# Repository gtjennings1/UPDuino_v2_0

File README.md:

# UPDuino_v2_0
UPDuino v2.0 - PCB Design Files, Designs, Documentation

UPDuino v2.0 is a small, low cost FPGA board.  
It is the same board as UPDuino v1.0, but v2.0 has a built-in USB programmer
(Similar to Arduino Pro Mini vs Arduino Nano microcontroller boards respectively).

Gnarly Grey UPDuino v2.0 Board Features

    Lattice UltraPlus FPGA
        5.3K LUTs, 1Mb SPRAM, 120Kb DPRAM, 8 Multipliers
        
    FTDI FT232H USB to SPI Device
    
    34 GPIO on 0.1” headers
    
    SPI Flash, RGB LED, 3.3V and 1.2V Regulators
    
    Open source schematic and layout using free Eagle PCB design tools
        Download Schematic & Layout
        Schematic PDF
        Programming Instructions
        RGB LED Example Project

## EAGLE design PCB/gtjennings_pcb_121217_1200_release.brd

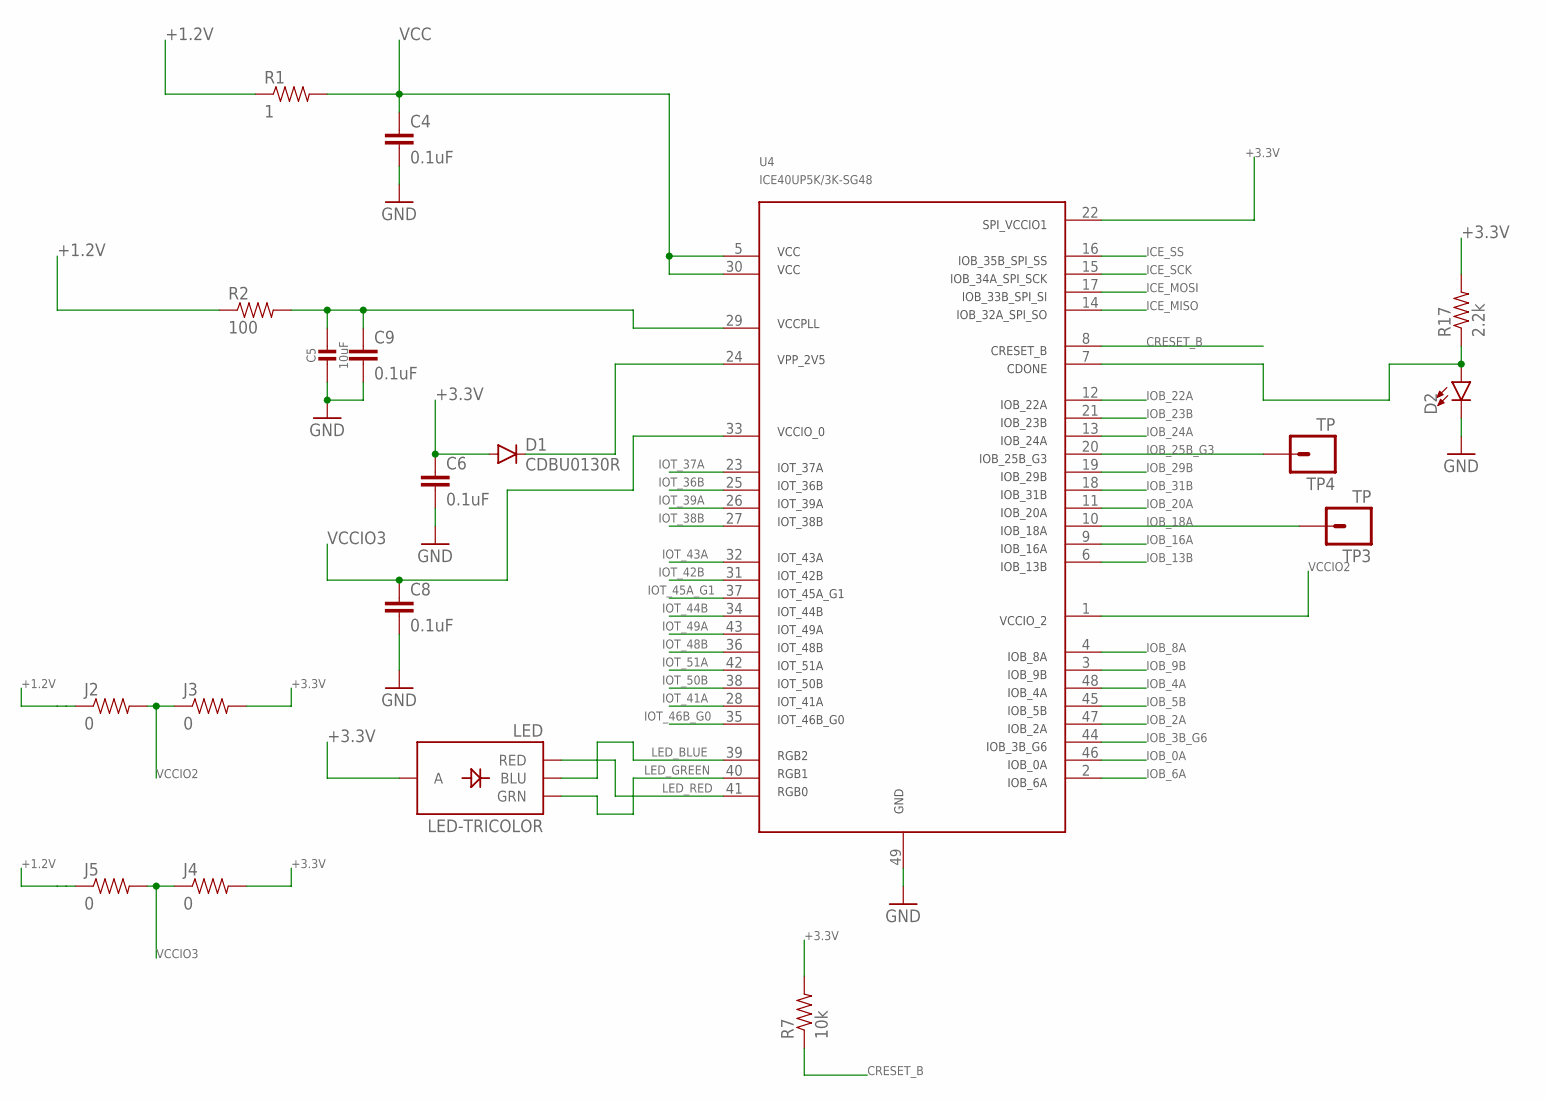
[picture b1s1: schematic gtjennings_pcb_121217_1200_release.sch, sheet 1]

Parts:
C4, C6, C8, C9: 0.1uF; 0603-CAP
C5: 10uF; 0603-NO
D1: CDBU0130R; SOD523
D2: LED0603; LED-0603
J2, J3, J4, J5: 0; 0603-RES
LED: LED-TRICOLOR; LED-TRICOLOR-SMD
R1: 1; 0603-RES
R2: 100; 0603-RES
R7: 10k; 0603-RES
R17: 2.2k; 0603-RES
TP3, TP4: TP
U4: ICE40UP5K/3K-SG48

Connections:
+1.2V: J2.1, J5.1, R1.1, R2.1; also elsewhere on the board
+3.3V: C6.1, D1.A, J3.2, J4.2, LED.A, R7.2, R17.2, U4.22; also elsewhere on the board
CRESET_B: R7.1, U4.8; also elsewhere on the board
GND: C4.2, C5.2, C6.2, C8.2, C9.2, D2.C, U4.49; also elsewhere on the board
ICE_MISO: U4.14; also elsewhere on the board
ICE_MOSI: U4.17; also elsewhere on the board
ICE_SCK: U4.15; also elsewhere on the board
ICE_SS: U4.16; also elsewhere on the board
IOB_0A: U4.46; also elsewhere on the board
IOB_2A: U4.47; also elsewhere on the board
IOB_3B_G6: U4.44; also elsewhere on the board
IOB_4A: U4.48; also elsewhere on the board
IOB_5B: U4.45; also elsewhere on the board
IOB_6A: U4.2; also elsewhere on the board
IOB_8A: U4.4; also elsewhere on the board
IOB_9B: U4.3; also elsewhere on the board
IOB_13B: U4.6; also elsewhere on the board
IOB_16A: U4.9; also elsewhere on the board
IOB_18A: TP3.1, U4.10
IOB_20A: U4.11; also elsewhere on the board
IOB_22A: U4.12; also elsewhere on the board
IOB_23B: U4.21; also elsewhere on the board
IOB_24A: U4.13; also elsewhere on the board
IOB_25B_G3: TP4.1, U4.20
IOB_29B: U4.19; also elsewhere on the board
IOB_31B: U4.18; also elsewhere on the board
IOT_36B: U4.25; also elsewhere on the board
IOT_37A: U4.23; also elsewhere on the board
IOT_38B: U4.27; also elsewhere on the board
IOT_39A: U4.26; also elsewhere on the board
IOT_41A: U4.28; also elsewhere on the board
IOT_42B: U4.31; also elsewhere on the board
IOT_43A: U4.32; also elsewhere on the board
IOT_44B: U4.34; also elsewhere on the board
IOT_45A_G1: U4.37; also elsewhere on the board
IOT_46B_G0: U4.35; also elsewhere on the board
IOT_48B: U4.36; also elsewhere on the board
IOT_49A: U4.43; also elsewhere on the board
IOT_50B: U4.38; also elsewhere on the board
IOT_51A: U4.42; also elsewhere on the board
LED_BLUE: LED.B (BLU), U4.39
LED_GREEN: LED.G (GRN), U4.40
LED_RED: LED.R (RED), U4.41
unnamed: C5.1, C9.1, R2.2, U4.29
unnamed: D1.C, U4.24
unnamed: D2.A, R17.1, U4.7
VCC: C4.1, R1.2, U4.5, U4.30
VCCIO2: J2.2, J3.1, U4.1
VCCIO3: C8.1, J4.1, J5.2, U4.33

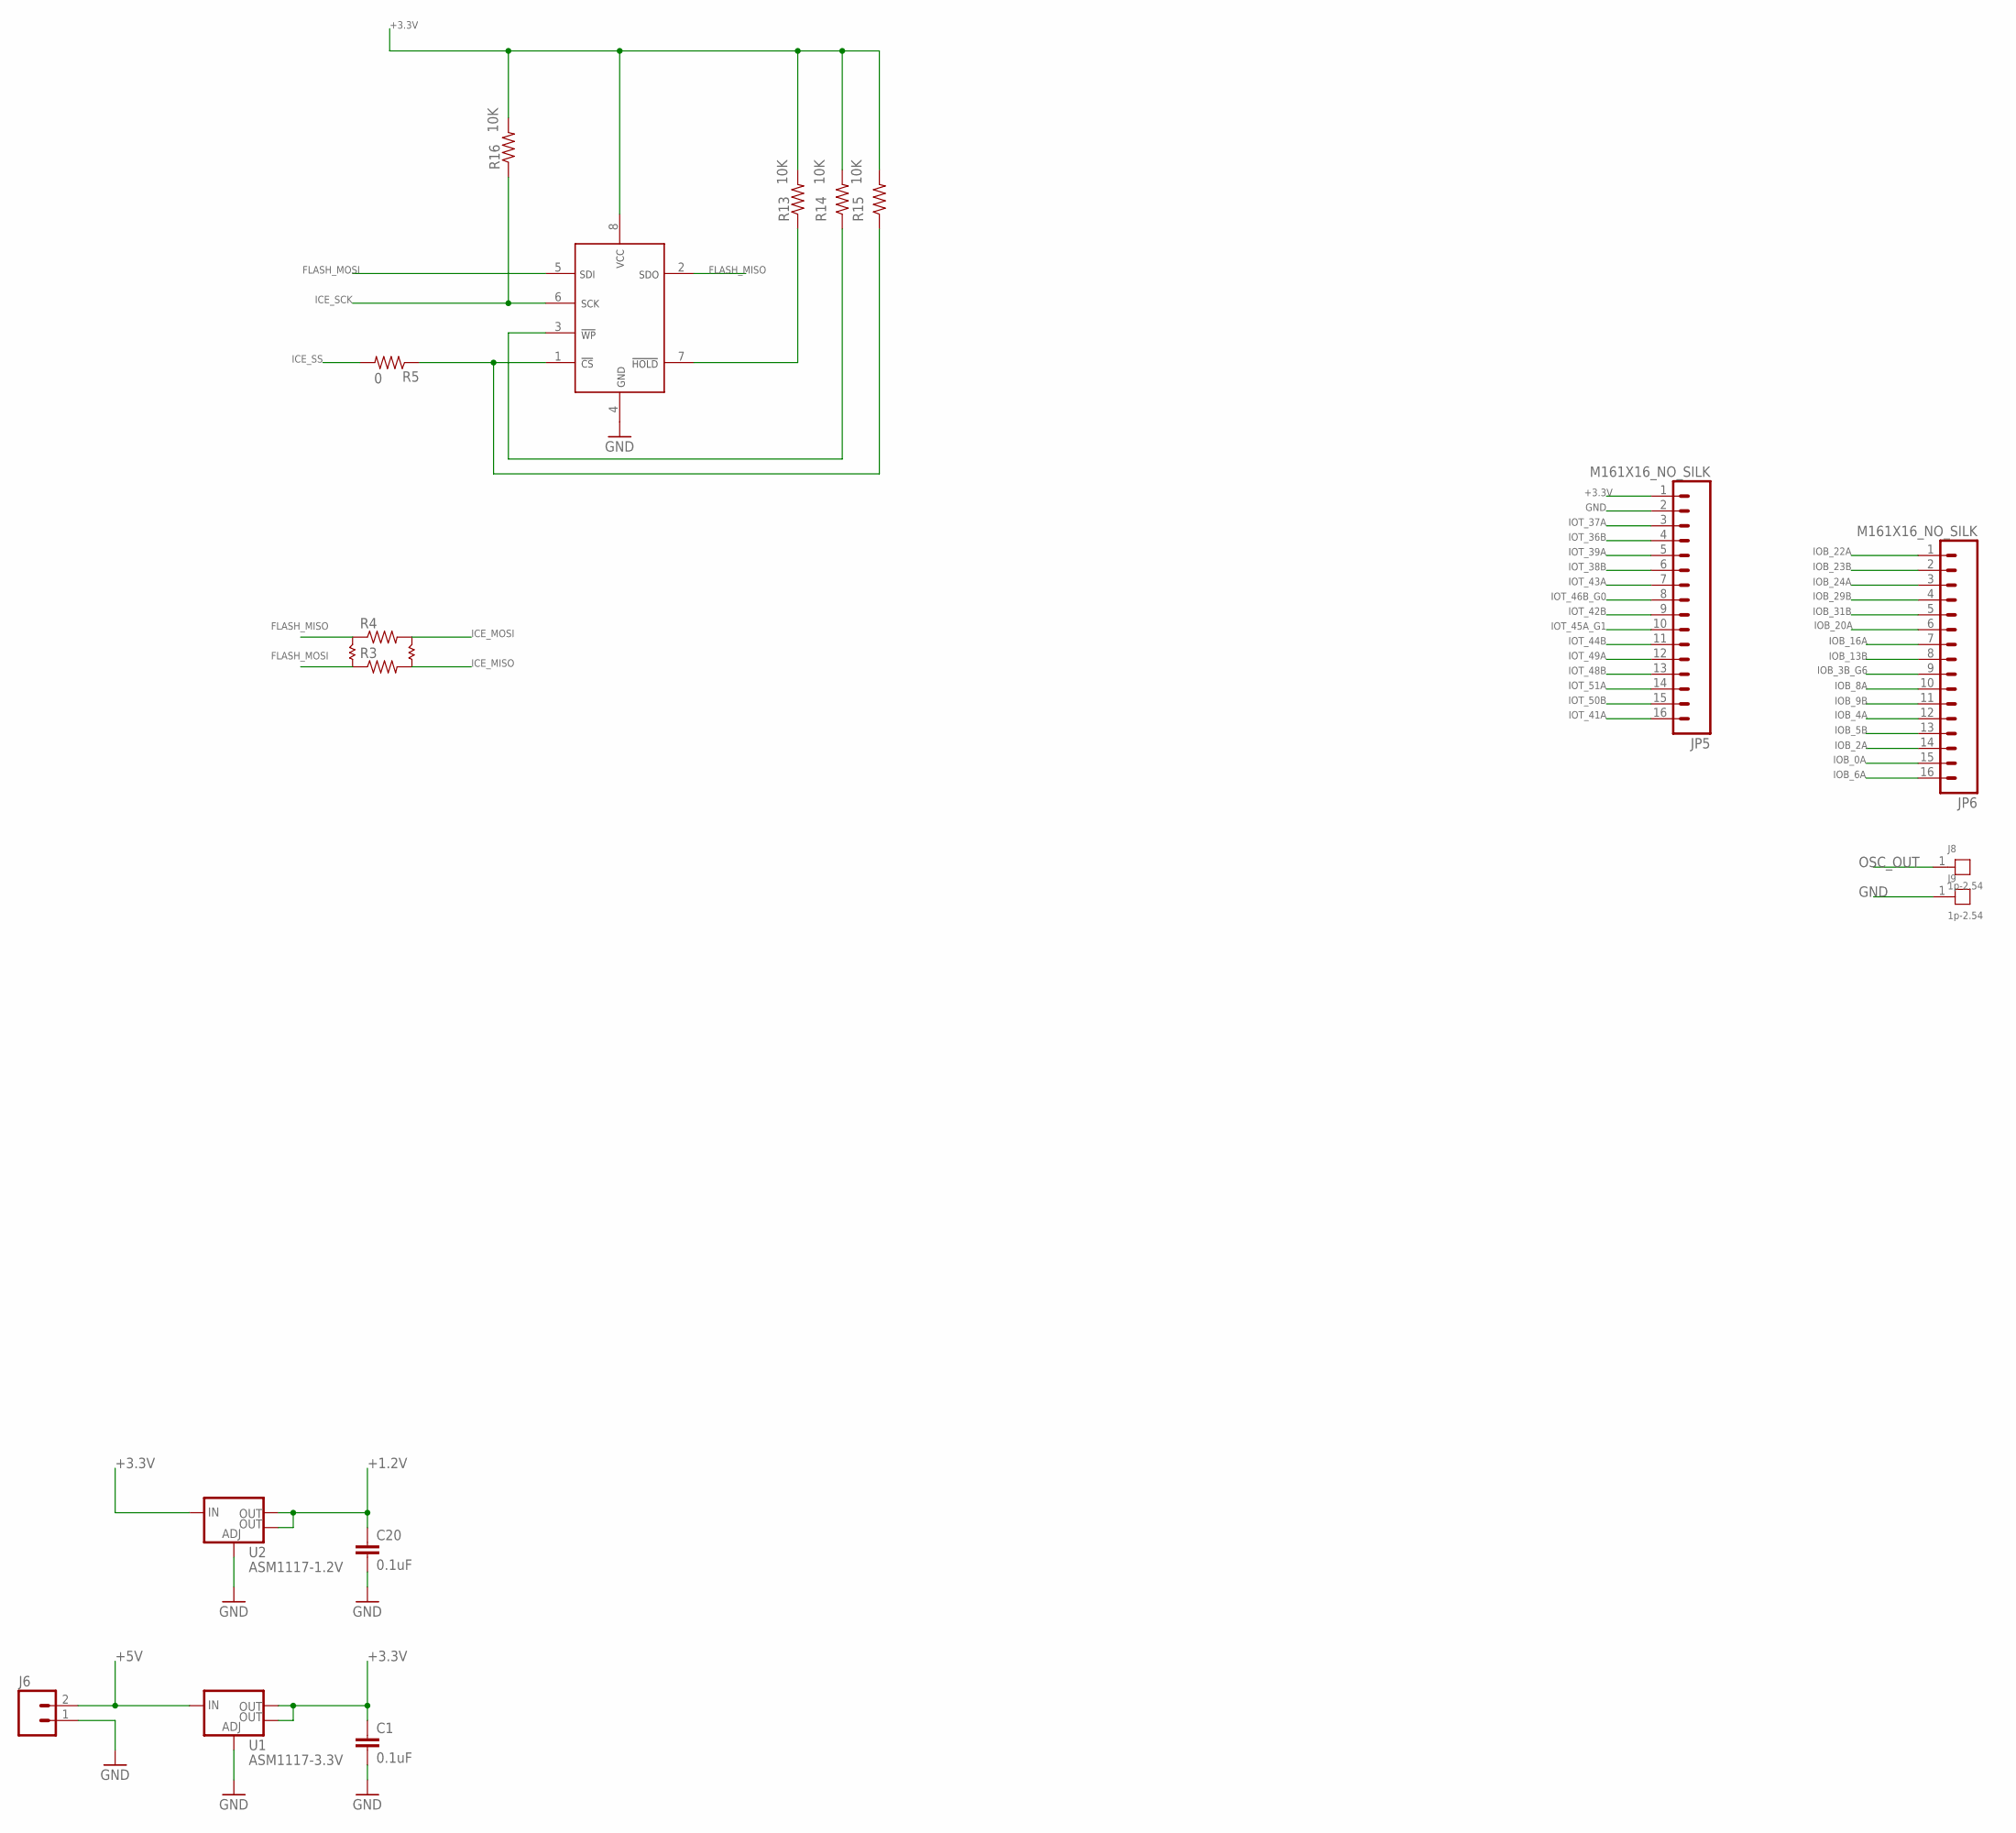
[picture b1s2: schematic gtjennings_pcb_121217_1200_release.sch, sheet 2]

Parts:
C1, C20: 0.1uF; 0603-CAP
J6: M02PTH; 1X02
J8, J9: 1p-2.54; 1P-65/35MIL
JP5, JP6: M161X16_NO_SILK; 1X16_NO_SILK
R3, R4: RESISTOR0805-RES; 0805
R5: 0; 0805
R13, R14, R15, R16: 10K; 0603-RES
U1: ASM1117-3.3V; SOT223
U2: ASM1117-1.2V; SOT223
U3: N25Q032A13ESC40F-ND; SO8

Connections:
+1.2V: C20.1, U2.2 (OUT), U2.4 (OUT); also elsewhere on the board
+3.3V: C1.1, JP5.1, R13.2, R14.2, R15.2, R16.2, U1.2 (OUT), U1.4 (OUT), U2.3 (IN), U3.8; also elsewhere on the board
+5V: J6.2, U1.3 (IN); also elsewhere on the board
FLASH_MISO: R4.1, U3.2; also elsewhere on the board
FLASH_MOSI: R3.1, U3.5; also elsewhere on the board
GND: C1.2, C20.2, J6.1, J9.1, JP5.2, U1.1 (ADJ), U2.1 (ADJ), U3.4; also elsewhere on the board
ICE_MISO: R3.2; also elsewhere on the board
ICE_MOSI: R4.2; also elsewhere on the board
ICE_SCK: R16.1, U3.6; also elsewhere on the board
ICE_SS: R5.2; also elsewhere on the board
IOB_0A: JP6.15; also elsewhere on the board
IOB_2A: JP6.14; also elsewhere on the board
IOB_3B_G6: JP6.9; also elsewhere on the board
IOB_4A: JP6.12; also elsewhere on the board
IOB_5B: JP6.13; also elsewhere on the board
IOB_6A: JP6.16; also elsewhere on the board
IOB_8A: JP6.10; also elsewhere on the board
IOB_9B: JP6.11; also elsewhere on the board
IOB_13B: JP6.8; also elsewhere on the board
IOB_16A: JP6.7; also elsewhere on the board
IOB_20A: JP6.6; also elsewhere on the board
IOB_22A: JP6.1; also elsewhere on the board
IOB_23B: JP6.2; also elsewhere on the board
IOB_24A: JP6.3; also elsewhere on the board
IOB_29B: JP6.4; also elsewhere on the board
IOB_31B: JP6.5; also elsewhere on the board
IOT_36B: JP5.4; also elsewhere on the board
IOT_37A: JP5.3; also elsewhere on the board
IOT_38B: JP5.6; also elsewhere on the board
IOT_39A: JP5.5; also elsewhere on the board
IOT_41A: JP5.16; also elsewhere on the board
IOT_42B: JP5.9; also elsewhere on the board
IOT_43A: JP5.7; also elsewhere on the board
IOT_44B: JP5.11; also elsewhere on the board
IOT_45A_G1: JP5.10; also elsewhere on the board
IOT_46B_G0: JP5.8; also elsewhere on the board
IOT_48B: JP5.13; also elsewhere on the board
IOT_49A: JP5.12; also elsewhere on the board
IOT_50B: JP5.15; also elsewhere on the board
IOT_51A: JP5.14; also elsewhere on the board
unnamed: R13.1, U3.7
unnamed: R14.1, U3.3
unnamed: R5.1, R15.1, U3.1
OSC_OUT: J8.1; also elsewhere on the board

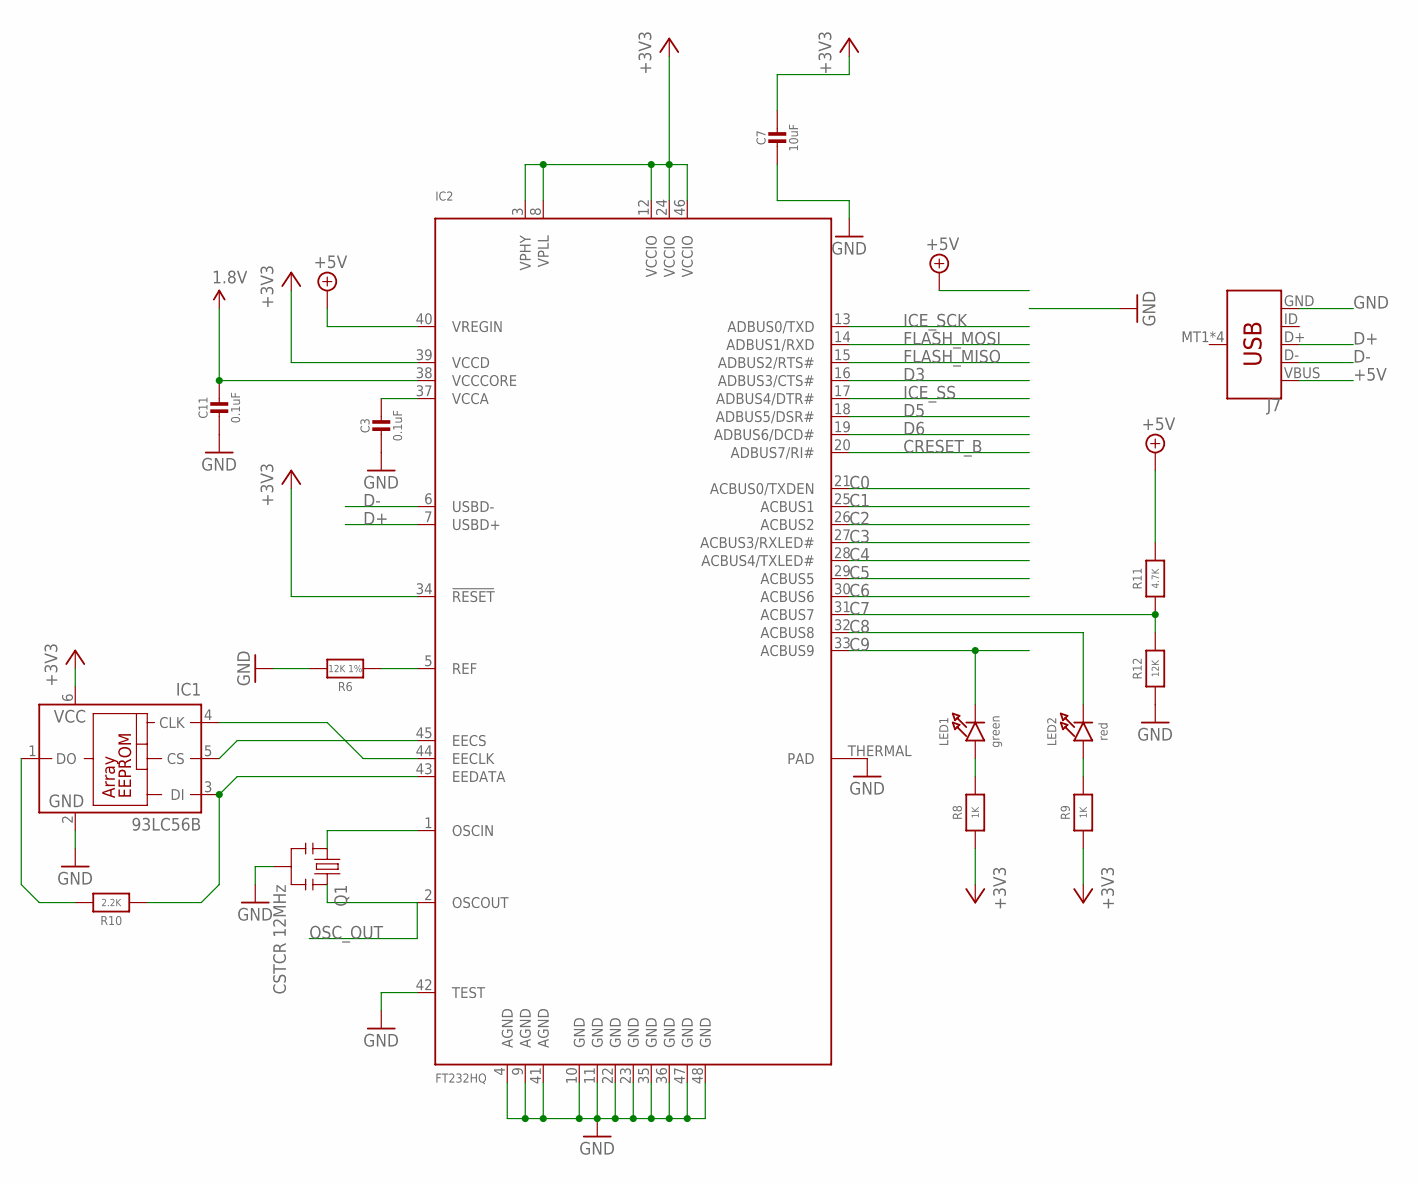
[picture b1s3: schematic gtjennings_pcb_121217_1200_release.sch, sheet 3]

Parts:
C3: 0.1uF; 0603-NO
C7: 10uF; 0603-NO
C11: 0.1uF; 0603-MINI
IC1: 93LC56B; SOT23-6
IC2: FT232HQ; QFN48_8MM
J7: USB_MICRO-B_SMT; USB-MICROB
LED1: green; CHIPLED_0805_NOOUTLINE
LED2: red; CHIPLED_0805_NOOUTLINE
Q1: CSTCR 12MHz; RESONATOR-SMD
R6: 12K 1%; _0603
R8, R9: 1K; 0603-MINI
R10: 2.2K; _0805MP
R11: 4.7K; 0603-MINI
R12: 12K; 0603-MINI

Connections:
1.8V: C11.1, IC2.38 (VCCCORE)
+3V3: C7.1, IC1.6 (VCC), IC2.3 (VPHY), IC2.8 (VPLL), IC2.12 (VCCIO), IC2.24 (VCCIO), IC2.34 (!RESET), IC2.39 (VCCD), IC2.46 (VCCIO), R8.1, R9.1
+5V: IC2.40 (VREGIN), J7.VBUS, R11.2; also elsewhere on the board
C0: IC2.21 (ACBUS0/TXDEN)
C1: IC2.25 (ACBUS1)
C2: IC2.26 (ACBUS2)
C3: IC2.27 (ACBUS3/RXLED#)
C4: IC2.28 (ACBUS4/TXLED#)
C5: IC2.29 (ACBUS5)
C6: IC2.30 (ACBUS6)
C7: IC2.31 (ACBUS7), R11.1, R12.2
C8: IC2.32 (ACBUS8), LED2.C
C9: IC2.33 (ACBUS9), LED1.C
CRESET_B: IC2.20 (ADBUS7/RI#); also elsewhere on the board
D3: IC2.16 (ADBUS3/CTS#)
D5: IC2.18 (ADBUS5/DSR#)
D6: IC2.19 (ADBUS6/DCD#)
D+: IC2.7 (USBD+), J7.D+
D-: IC2.6 (USBD-), J7.D-
FLASH_MISO: IC2.15 (ADBUS2/RTS#); also elsewhere on the board
FLASH_MOSI: IC2.14 (ADBUS1/RXD); also elsewhere on the board
GND: C3.2, C7.2, C11.2, IC1.2 (GND), IC2.4 (AGND), IC2.9 (AGND), IC2.10 (GND), IC2.11 (GND), IC2.22 (GND), IC2.23 (GND), IC2.35 (GND), IC2.36 (GND), IC2.41 (AGND), IC2.42 (TEST), IC2.47 (GND), IC2.48 (GND), IC2.THERMAL (PAD), J7.GND, Q1.2, R6.2, R12.1; also elsewhere on the board
ICE_SCK: IC2.13 (ADBUS0/TXD); also elsewhere on the board
ICE_SS: IC2.17 (ADBUS4/DTR#); also elsewhere on the board
unnamed: IC2.1 (OSCIN), Q1.1
unnamed: IC2.5 (REF), R6.1
unnamed: LED2.A, R9.2
unnamed: LED1.A, R8.2
unnamed: IC1.3 (DI), IC2.43 (EEDATA), R10.1
unnamed: IC1.5 (CS), IC2.45 (EECS)
unnamed: IC1.4 (CLK), IC2.44 (EECLK)
unnamed: IC1.1 (DO), R10.2
OSC_OUT: IC2.2 (OSCOUT), Q1.3; also elsewhere on the board
VCCA: C3.1, IC2.37 (VCCA)

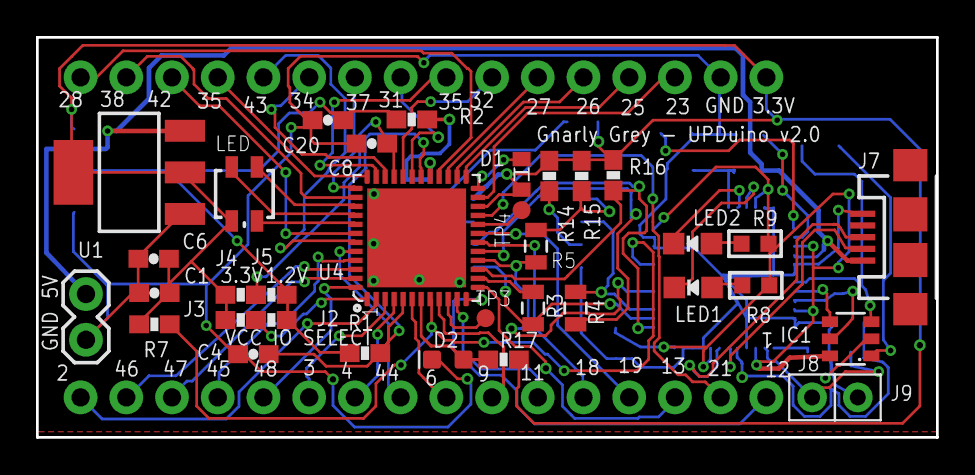
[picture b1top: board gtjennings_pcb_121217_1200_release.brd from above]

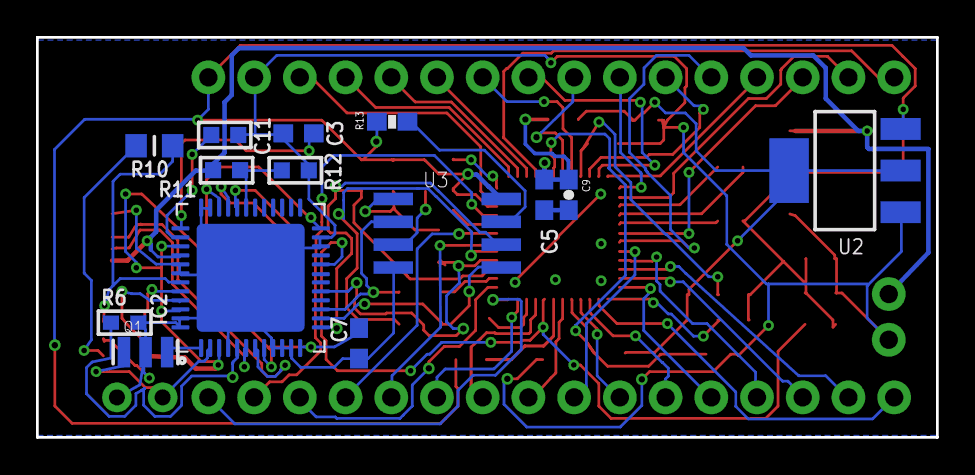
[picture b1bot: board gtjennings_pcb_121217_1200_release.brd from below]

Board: 2 copper layers, 50.0 x 22.2 mm, 51 parts (14 on the bottom side), 72 nets.

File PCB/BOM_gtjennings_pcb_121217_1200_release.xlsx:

EXAMPLE BILL OF MATERIALS (BOM)
Place your mouse over the red comment markers in the top right corner of the ce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
1 | 2 | 3 | 4 | 5 | 6 | 7 | 8 | 9 | 10 | 11
Sequential Item Nos | Consolidated quantity of each Part No | Component ID's separated by Commas | Confirmation Yes or No Parts are fitted this Build (Note 1) | Full Description of Part e.g. for capacitor include value, tolerance and type o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 | Value or Type No | Case Style | Supplier or Manufacturer (Note 2) | Supplier Stock No or Manufacturer's Part No (Note 2) | Side of Board Mounted | PTH or SMT
Item | Qty | Reference | Fit | Part Description | Value | Package | Supplier | Supplier Ref | Side | Mount Type
1 | 6 | C1,C3,C6,C8,C11,C20,C9 | Y | Capacitors | 0.1uF | 0603-CAP |  |  |  | S
2 | 1 | C7,C5 | y | Capacitors | 10uF | 0603-CAP
3 | 1 | D1 | Y | Diode | CDBU0130R | SOD523 |  |  |  | S
4 | 1 | D2 | Y | GREEN LED_0603 | APT1608SGC | 0603_LED
5 | 0 | J6,JP5,JP6 | N | Connectors | DNI | 0603-RES |  |  |  | P
6 | 2 | J3, J4 | Y | Resistors | 0 | 0603-RES
7 | 0 | J2, J5 | N | Resistors | DNI | 0603-RES |  |  |  | S
8 | 1 | J7 | Y | USB connector | USB-MicroB | 10118192-0001LF |  | 10118192-0001LF
9 | 1 | LED | Y | LED | LED-TRICOLOR | LED-TRICOLOR-SMD |  | CLV1L-FKB-CHMMQEHBB7673673CT-ND | T | S
10 | 1 | R1 | Y | Resistors | 1 | 0603-RES |  |  |  | S
11 | 2 | R2,R17 | Y | Resistors | 100 | 0603-RES |  |  |  | S
12 | 1 | R3 | Y | Resistors | 0 | 0603-RES |  |  |  | P
13 | 2 | R4,R5 | Y | Resistors | 0 | 0805-RES |  |  |  | P
14 | 1 | R6 | Y | Resistors | 12k 1% | 0603-RES
15 | 5 | R7,R13,R14,R15,R16 | Y | Resistors | 10k | 0603-RES |  |  |  | S
16 | 2 | R8,R9 | Y | Resistors | 1k | 0603-RES
17 | 1 | R10 | Y | Resistors | 2.2k | 0603-RES
18 | 1 | R11 | Y | Resistors | 4.7k | 0603-RES
19 | 1 | R12 | Y | Resistors | 12k | 0603-RES
20 | 1 | U1 | Y | PowerIC | ASM1117-3.3 | SOT223 |  | ASM1117-3.3 | T | S
21 | 1 | U2 | Y | PowerIC | ASM1117-1.2 | SOT223 |  | ASM1117-1.2 | B | S
22 | 1 | U3 | Y | 25Q32 | 25Q32 | SO8 | Winbond Electronics | 25Q32 | B | S
23 | 1 | U4 | Y | ICE40UP5K-3K-SG48 | ICE40UP5K/3K-SG48 | ICE40UP5K/3K-SG48 | Lattice Semiconductor | ICE40UP5K/3K-SG48 | T | S
24 | 1 | IC1 | Y | Memory IC | 93LC56B | SOT23-6
25 | 1 | IC2 | Y | FT232HQ IC | FT232HQ | QFN48_8MM
26 | 1 | Q1 | Y | Resonator_smd | CSTCR 12MHz | CSTCE12M0G55-R0
 | 37

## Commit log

2019-10-04 docx -> md
2019-10-04 Cleanup

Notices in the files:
parts and their libraries:
SparkFun-Resistors: Licensing: Creative Commons ShareAlike 4.0 International - https://creativecommons.org/licenses/by-sa/4.0
microbuilder: This work is placed in the public domain, and may be freely used for commercial and non-commercial work with the following conditions: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
